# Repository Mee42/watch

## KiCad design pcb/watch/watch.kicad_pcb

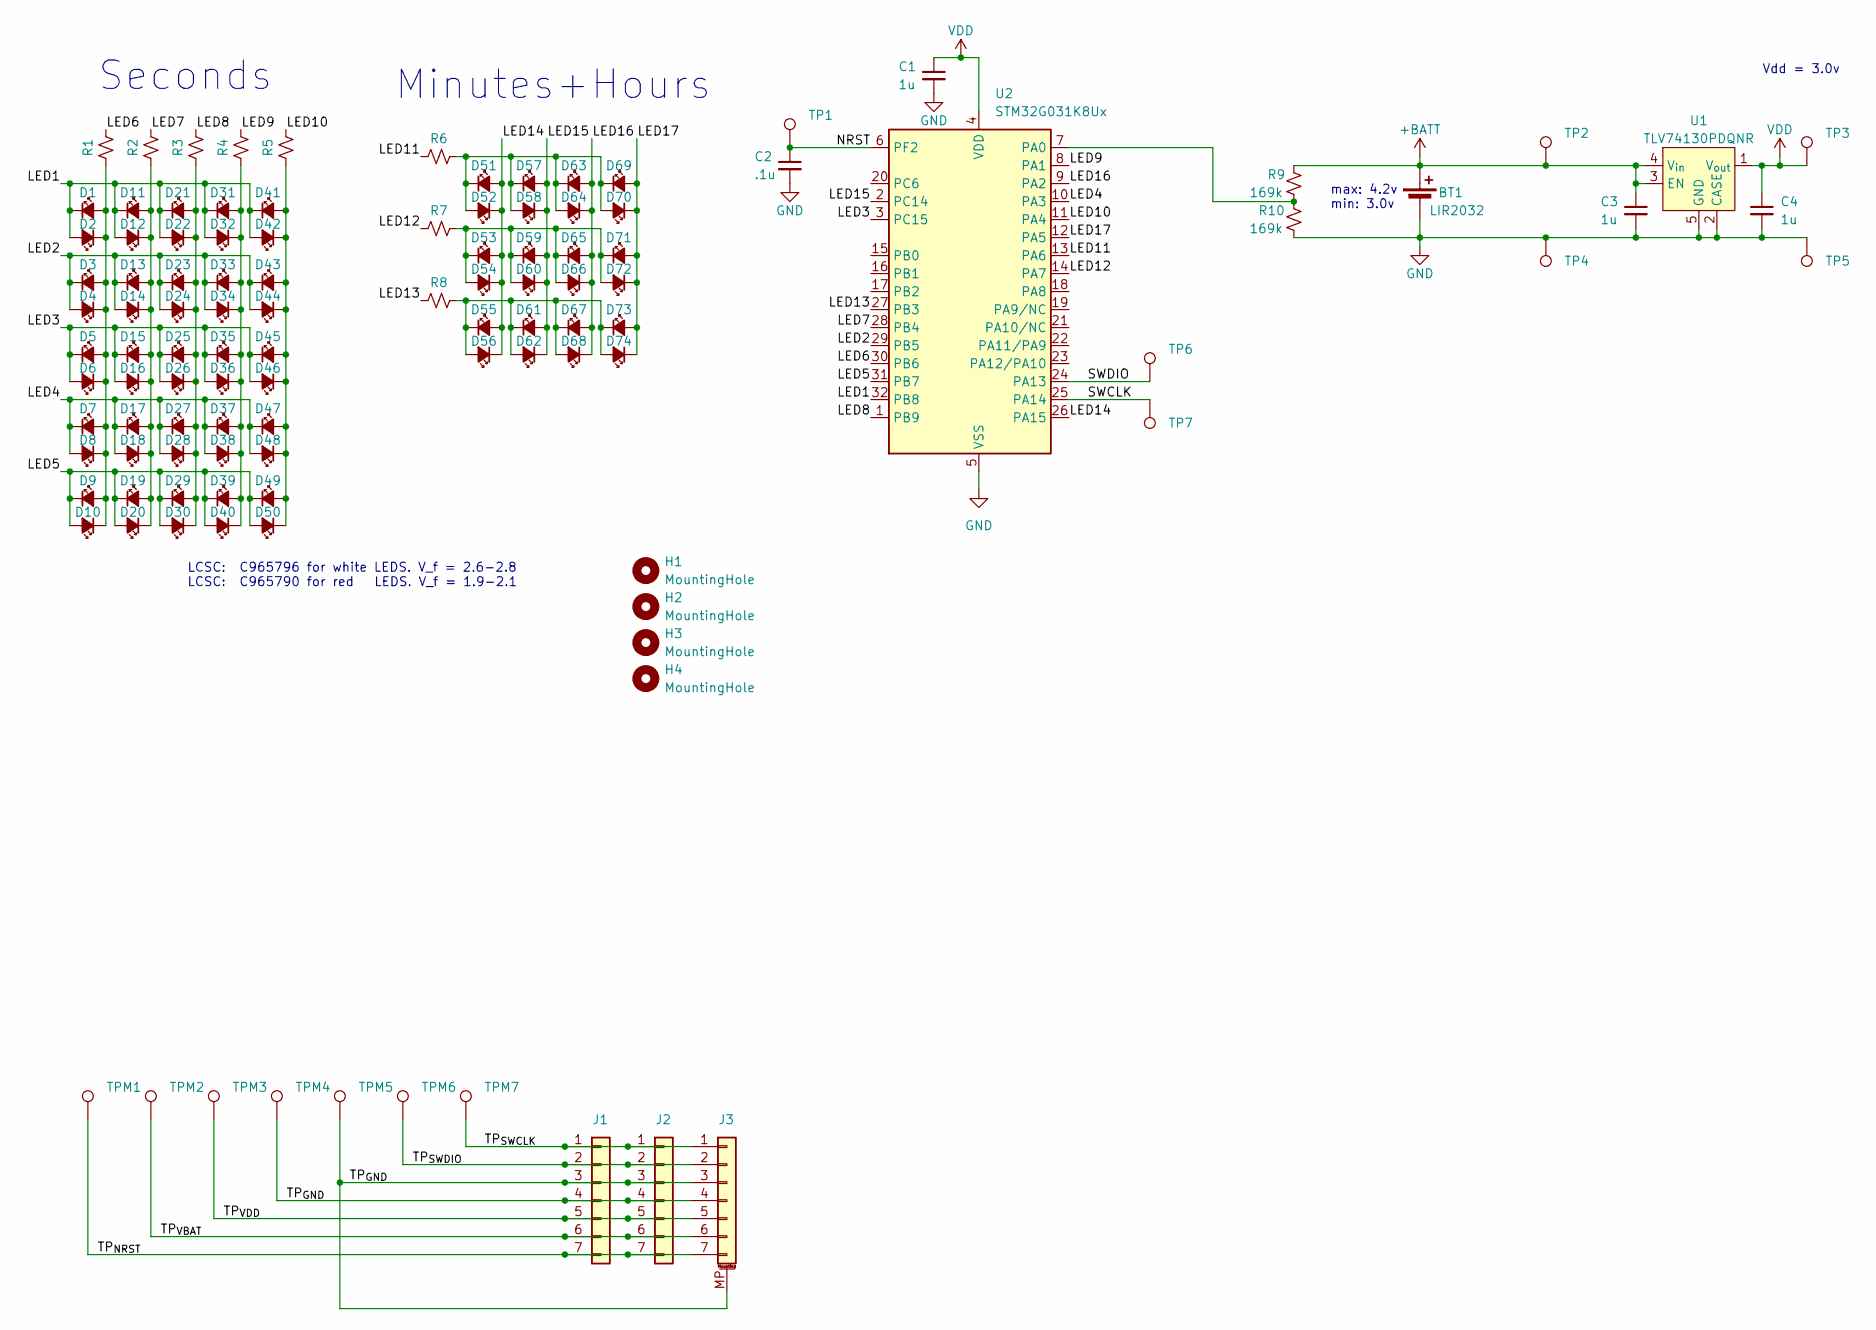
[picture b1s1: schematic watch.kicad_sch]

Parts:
BT1: LIR2032; bat_holder
C1, C3, C4: 1u; C_0402_nosilk
C2: .1u; C_0402_nosilk
D1, D11, D21, D31, D41, D51: LED_Small_Filled; LED_0402_1005Metric
D2, D3, D4, D5, D6, D7, D8, D9, D10, D12, D13, D14, D15, D16, D17, D18, D19, D20, D22, D23, D24, D25, D26, D27, D28, D29, D30, D32, D33, D34, D35, D36, D37, D38, D39, D40, D42, D43, D44, D45, D46, D47, D48, D49, D50, D52, D53, D54, D55, D56, D57, D58, D59, D60, D61, D62, D63, D64, D65, D66, D67, D68, D69, D70, D71, D72, D73, D74: LED_Small_Filled; LED_0402_nosilk
H1, H2, H3, H4: MountingHole; m1.4_hole
J1, J2: Conn_01x07; mypinheader
J3: Conn_01x07_MountingPin; JST_GH_SM07B-GHS-TB_1x07-1MP_P1.25mm_Horizontal
R1, R2, R3, R4, R5: R_Small_US; R_0402_nosilk_square
R6, R7, R8: R_Small_US; R_0402_nosilk
R9, R10: 169k; LED_0402_nosilk
TP1, TP2, TP3, TP6, TP7: TestPoint; testpoint_better
TP4, TP5: TestPoint; testpoint_better_square
TPM1, TPM2, TPM3, TPM4, TPM5, TPM6, TPM7: TestPoint; pogo
U1: TLV74130PDQNR; Texas_X2SON_nosilk
U2: STM32G031K8Ux; UFQFPN-32-nosilk

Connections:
+BATT: BT1.1 (+), C3.1, R9.1, TP2.1, U1.3 (EN), U1.4 (V_{in})
/LED1: D1.1 (K), D2.2 (A), D11.1 (K), D12.2 (A), D21.1 (K), D22.2 (A), D31.1 (K), D32.2 (A), D41.1 (K), D42.2 (A), U2.32 (PB8)
/LED2: D3.1 (K), D4.2 (A), D13.1 (K), D14.2 (A), D23.1 (K), D24.2 (A), D33.1 (K), D34.2 (A), D43.1 (K), D44.2 (A), U2.29 (PB5)
/LED3: D5.1 (K), D6.2 (A), D15.1 (K), D16.2 (A), D25.1 (K), D26.2 (A), D35.1 (K), D36.2 (A), D45.1 (K), D46.2 (A), U2.3 (PC15)
/LED4: D7.1 (K), D8.2 (A), D17.1 (K), D18.2 (A), D27.1 (K), D28.2 (A), D37.1 (K), D38.2 (A), D47.1 (K), D48.2 (A), U2.10 (PA3)
/LED5: D9.1 (K), D10.2 (A), D19.1 (K), D20.2 (A), D29.1 (K), D30.2 (A), D39.1 (K), D40.2 (A), D49.1 (K), D50.2 (A), U2.31 (PB7)
/LED6: R1.2, U2.30 (PB6)
/LED7: R2.2, U2.28 (PB4)
/LED8: R3.2, U2.1 (PB9)
/LED9: R4.2, U2.8 (PA1)
/LED10: R5.2, U2.11 (PA4)
/LED11: R6.1, U2.13 (PA6)
/LED12: R7.1, U2.14 (PA7)
/LED13: R8.1, U2.27 (PB3)
/LED14: D51.2 (A), D52.1 (K), D53.2 (A), D54.1 (K), D55.2 (A), D56.1 (K), U2.26 (PA15)
/LED15: D57.2 (A), D58.1 (K), D59.2 (A), D60.1 (K), D61.2 (A), D62.1 (K), U2.2 (PC14)
/LED16: D63.2 (A), D64.1 (K), D65.2 (A), D66.1 (K), D67.2 (A), D68.1 (K), U2.9 (PA2)
/LED17: D69.2 (A), D70.1 (K), D71.2 (A), D72.1 (K), D73.2 (A), D74.1 (K), U2.12 (PA5)
/NRST: C2.1, TP1.1, U2.6 (PF2)
/SWCLK: TP7.1, U2.25 (PA14)
/SWDIO: TP6.1, U2.24 (PA13)
/TP_{GND}: J1.3, J1.4, J2.3, J2.4, J3.3, J3.4, J3.MP (MountPin), TPM4.1, TPM5.1
/TP_{NRST}: J1.7, J2.7, J3.7, TPM1.1
/TP_{SWCLK}: J1.1, J2.1, J3.1, TPM7.1
/TP_{SWDIO}: J1.2, J2.2, J3.2, TPM6.1
/TP_{VBAT}: J1.6, J2.6, J3.6, TPM2.1
/TP_{VDD}: J1.5, J2.5, J3.5, TPM3.1
GND: BT1.2 (-), C1.2, C2.2, C3.2, C4.2, R10.2, TP4.1, TP5.1, U1.2 (CASE), U1.5 (GND), U2.5 (VSS), U2.33 (VSS)
unnamed: D1.2 (A), D2.1 (K), D3.2 (A), D4.1 (K), D5.2 (A), D6.1 (K), D7.2 (A), D8.1 (K), D9.2 (A), D10.1 (K), R1.1
unnamed: D11.2 (A), D12.1 (K), D13.2 (A), D14.1 (K), D15.2 (A), D16.1 (K), D17.2 (A), D18.1 (K), D19.2 (A), D20.1 (K), R2.1
unnamed: D21.2 (A), D22.1 (K), D23.2 (A), D24.1 (K), D25.2 (A), D26.1 (K), D27.2 (A), D28.1 (K), D29.2 (A), D30.1 (K), R3.1
unnamed: D31.2 (A), D32.1 (K), D33.2 (A), D34.1 (K), D35.2 (A), D36.1 (K), D37.2 (A), D38.1 (K), D39.2 (A), D40.1 (K), R4.1
unnamed: D41.2 (A), D42.1 (K), D43.2 (A), D44.1 (K), D45.2 (A), D46.1 (K), D47.2 (A), D48.1 (K), D49.2 (A), D50.1 (K), R5.1
unnamed: D51.1 (K), D52.2 (A), D57.1 (K), D58.2 (A), D63.1 (K), D64.2 (A), D69.1 (K), D70.2 (A), R6.2
unnamed: D53.1 (K), D54.2 (A), D59.1 (K), D60.2 (A), D65.1 (K), D66.2 (A), D71.1 (K), D72.2 (A), R7.2
unnamed: D55.1 (K), D56.2 (A), D61.1 (K), D62.2 (A), D67.1 (K), D68.2 (A), D73.1 (K), D74.2 (A), R8.2
unnamed: R9.2, R10.1, U2.7 (PA0)
VDD: C1.1, C4.1, TP3.1, U1.1 (V_{out}), U2.4 (VDD)

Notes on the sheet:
Seconds
Vdd = 3.0v
max: 4.2v min: 3.0v
Minutes+Hours
LCSC: C965796 for white LEDS. V_f = 2.6-2.8 LCSC: C965790 for red LEDS. V_f = 1.9-2.1

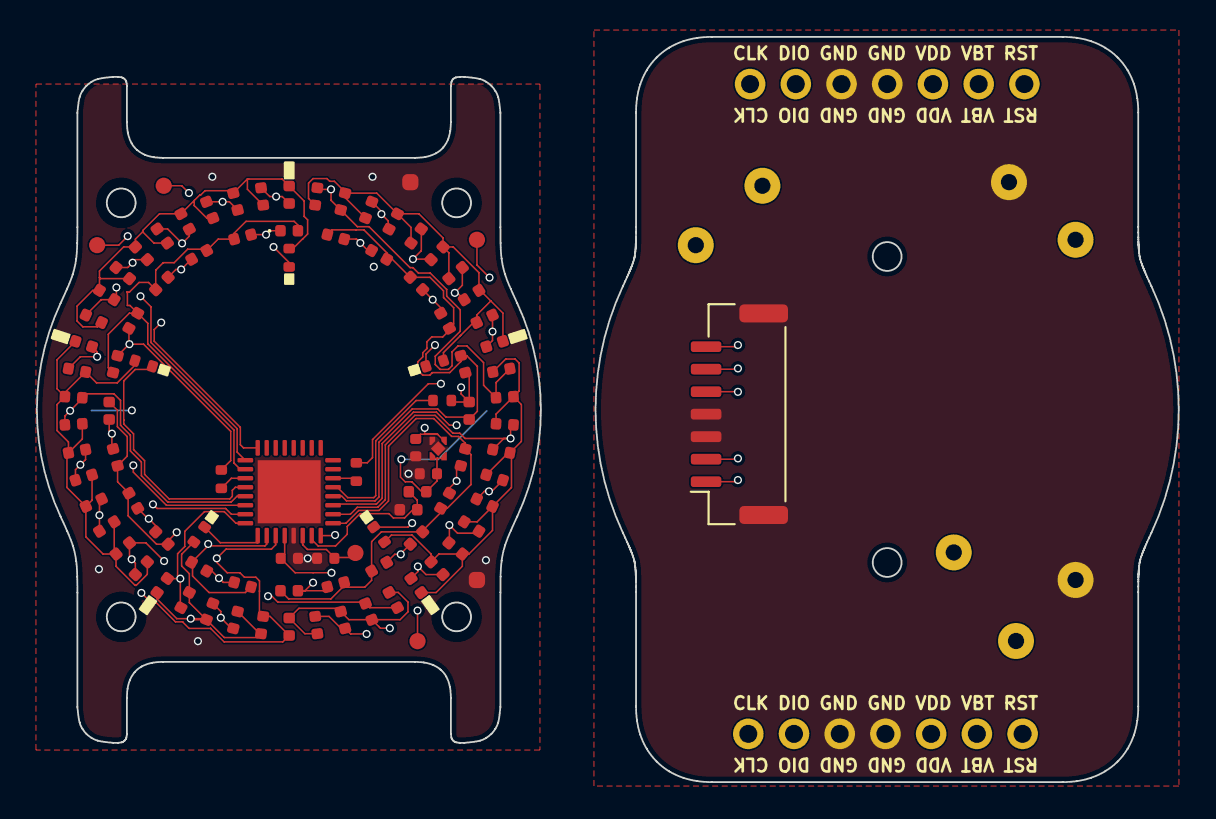
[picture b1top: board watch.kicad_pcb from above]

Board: 8 copper layers, 28.0 x 37.0 mm, 112 parts (1 on the bottom side), 38 nets.

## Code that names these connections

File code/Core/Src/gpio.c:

/* USER CODE BEGIN Header */
/**
  ******************************************************************************
  * @file    gpio.c
  * @brief   This file provides code for the configuration
  *          of all used GPIO pins.
  ******************************************************************************
  * @attention
  *
  * Copyright (c) 2023 STMicroelectronics.
  * All rights reserved.
  *
  * This software is licensed under terms that can be found in the LICENSE file
  * in the root directory of this software component.
  * If no LICENSE file comes with this software, it is provided AS-IS.
  *
  ******************************************************************************
  */
/* USER CODE END Header */

/* Includes ------------------------------------------------------------------*/
#include "gpio.h"

/* USER CODE BEGIN 0 */

/* USER CODE END 0 */

/*----------------------------------------------------------------------------*/
/* Configure GPIO                                                             */
/*----------------------------------------------------------------------------*/
/* USER CODE BEGIN 1 */

/* USER CODE END 1 */

/** Configure pins
*/
void MX_GPIO_Init(void)
{

  GPIO_InitTypeDef GPIO_InitStruct = {0};

  /* GPIO Ports Clock Enable */
  __HAL_RCC_GPIOB_CLK_ENABLE();
  __HAL_RCC_GPIOC_CLK_ENABLE();
  __HAL_RCC_GPIOF_CLK_ENABLE();
  __HAL_RCC_GPIOA_CLK_ENABLE();

  /*Configure GPIO pins : PB9 PB0 PB1 PB2
                           PB3 PB4 PB5 PB6
                           PB7 PB8 */
  GPIO_InitStruct.Pin = GPIO_PIN_9|GPIO_PIN_0|GPIO_PIN_1|GPIO_PIN_2
                          |GPIO_PIN_3|GPIO_PIN_4|GPIO_PIN_5|GPIO_PIN_6
                          |GPIO_PIN_7|GPIO_PIN_8;
  GPIO_InitStruct.Mode = GPIO_MODE_ANALOG;
  GPIO_InitStruct.Pull = GPIO_NOPULL;
  HAL_GPIO_Init(GPIOB, &GPIO_InitStruct);

  /*Configure GPIO pins : PC14 PC15 PC6 */
  GPIO_InitStruct.Pin = GPIO_PIN_14|GPIO_PIN_15|GPIO_PIN_6;
  GPIO_InitStruct.Mode = GPIO_MODE_ANALOG;
  GPIO_InitStruct.Pull = GPIO_NOPULL;
  HAL_GPIO_Init(GPIOC, &GPIO_InitStruct);

  /*Configure GPIO pin : PF2 */
  GPIO_InitStruct.Pin = GPIO_PIN_2;
  GPIO_InitStruct.Mode = GPIO_MODE_ANALOG;
  GPIO_InitStruct.Pull = GPIO_NOPULL;
  HAL_GPIO_Init(GPIOF, &GPIO_InitStruct);

  /*Configure GPIO pins : PA0 PA1 PA2 PA3
                           PA4 PA5 PA6 PA7
                           PA8 PA9 PA10 PA11
                           PA12 PA13 PA14 PA15 */
  GPIO_InitStruct.Pin = GPIO_PIN_0|GPIO_PIN_1|GPIO_PIN_2|GPIO_PIN_3
                          |GPIO_PIN_4|GPIO_PIN_5|GPIO_PIN_6|GPIO_PIN_7
                          |GPIO_PIN_8|GPIO_PIN_9|GPIO_PIN_10|GPIO_PIN_11
                          |GPIO_PIN_12|GPIO_PIN_13|GPIO_PIN_14|GPIO_PIN_15;
  GPIO_InitStruct.Mode = GPIO_MODE_ANALOG;
  GPIO_InitStruct.Pull = GPIO_NOPULL;
  HAL_GPIO_Init(GPIOA, &GPIO_InitStruct);

}

/* USER CODE BEGIN 2 */

/* USER CODE END 2 */

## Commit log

2023-09-28 removed license
2023-09-28 intitial commit
2023-10-14 fuck fuck fuck I made it too small
2023-10-16 eeeee
2023-10-26 better outline
2023-11-22 rev1 lol
2023-12-05 repo
2024-01-19 fuck this lol
2024-01-30 rev2 final commit
2024-01-30 rev2 final
